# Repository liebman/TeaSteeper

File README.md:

# TeaSteeper

TeaSteeper is a simple device to prevent tea from being over steeped.

- [src](src) contains firmware sources
- [kicad](kicad) contains [KiCad](https://www.kicad.org/) design files
- [enclosure](enclosure) contains [FreeCad](https://www.freecadweb.org/) and STL files for the enclosure.
These are designed for a FDM printer with a .4mm nozzle and .2mm layer height.

## Firmware

This project uses [PlatformIO](https://platformio.org/) to build firmware.

## Schematic

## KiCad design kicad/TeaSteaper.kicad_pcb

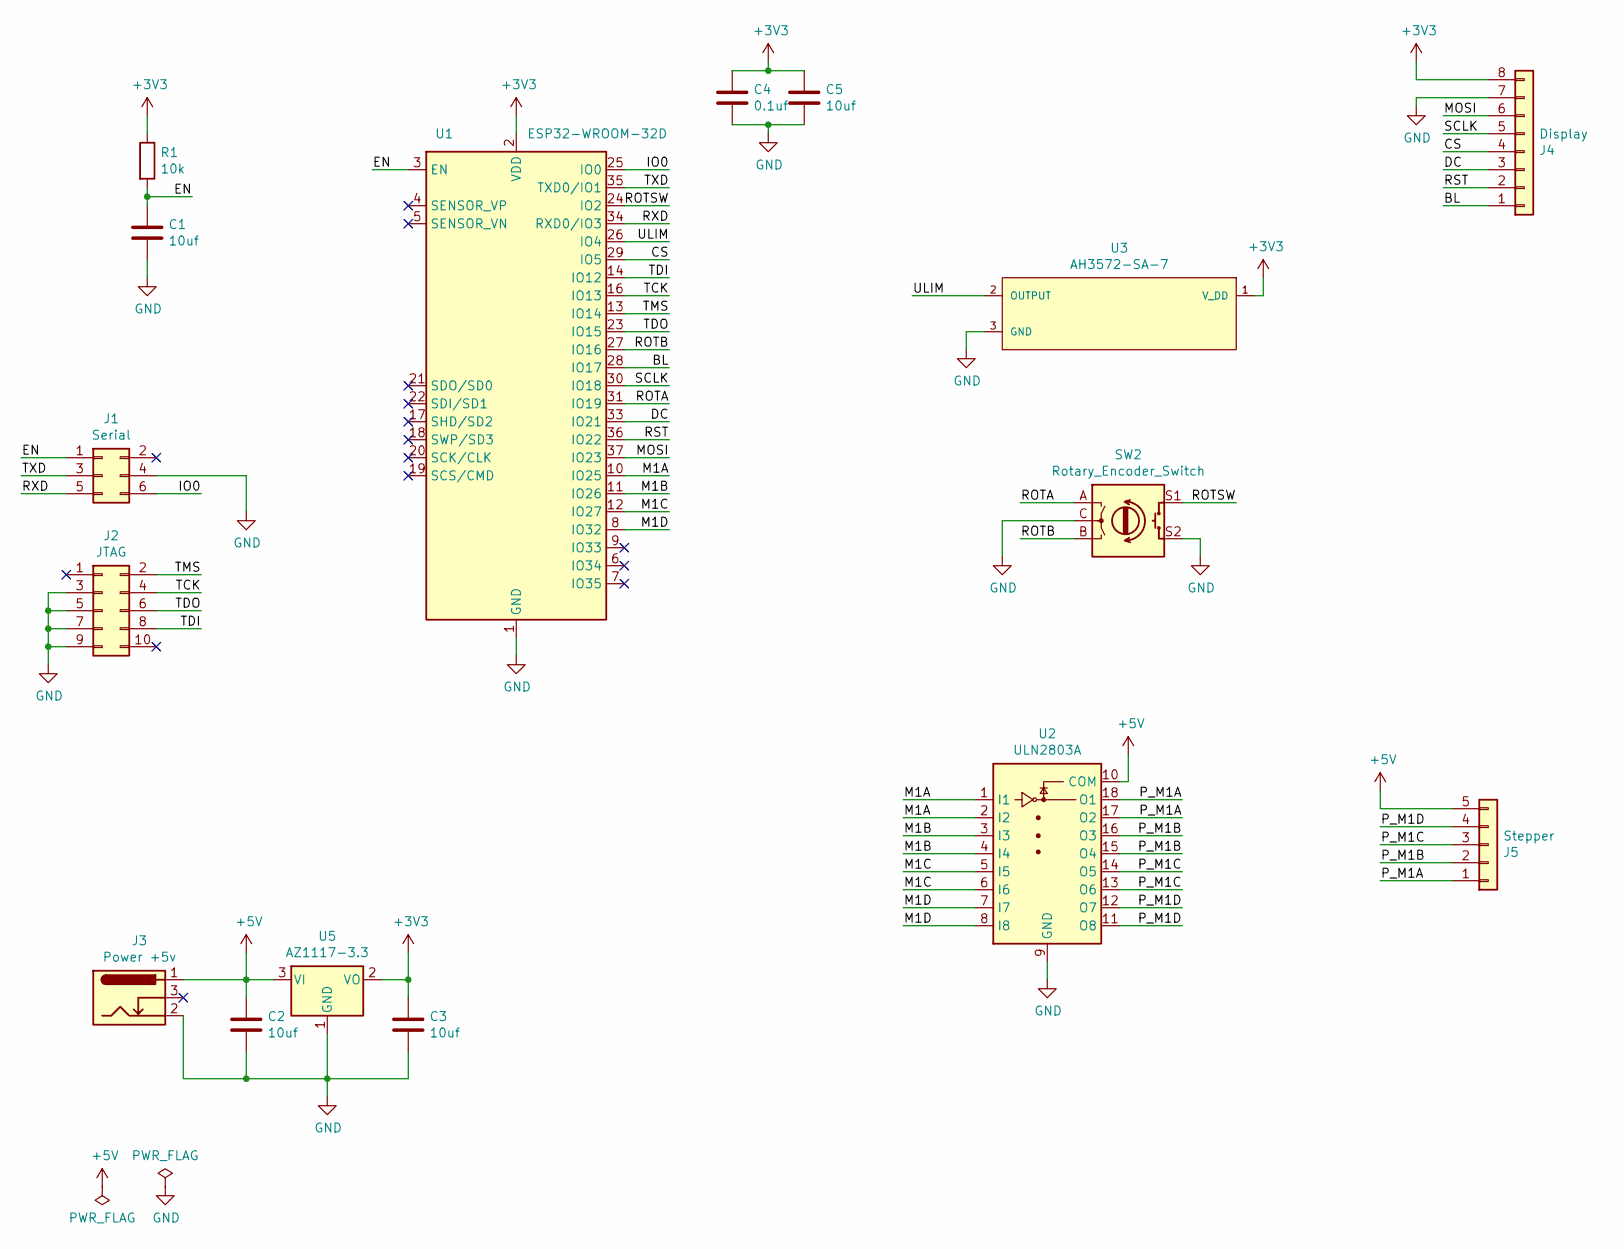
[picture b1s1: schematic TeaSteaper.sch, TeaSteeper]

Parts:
C1, C2, C3, C5: 10uf; C_0805_2012Metric_Pad1.18x1.45mm_HandSolder
C4: 0.1uf; C_0805_2012Metric_Pad1.18x1.45mm_HandSolder
J1: Serial; IDC-Header_2x03_P2.54mm_Vertical
J2: JTAG; IDC-Header_2x05_P2.54mm_Vertical
J3: Power +5v; BarrelJack_CUI_PJ-202A_Horizontal
J4: Display; JST_PH_B8B-PH-K_1x08_P2.00mm_Vertical
J5: Stepper; JST_XH_B5B-XH-A_1x05_P2.50mm_Vertical
R1: 10k; R_0805_2012Metric_Pad1.20x1.40mm_HandSolder
SW2: Rotary_Encoder_Switch; RotaryEncoder_Alps_EC11E-Switch_Vertical_H20mm
U1: ESP32-WROOM-32D; ESP32-WROOM-32
U2: ULN2803A; SOIC-18W_7.5x11.6mm_P1.27mm
U3: AH3572-SA-7; SOT-23; mouser part number 621-AH3572-SA-7; digikey description MAG SWITCH OMNIPOLAR SOT23 T&R
U5: AZ1117-3.3; SOT-223-3_TabPin2

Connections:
+3V3: C3.1, C4.1, C5.1, J4.8, R1.1, U1.2 (VDD), U3.1 (V_DD), U5.2 (VO)
+5V: C2.1, J3.1, J5.5, U2.10 (COM), U5.3 (VI)
/BL: J4.1, U1.28 (IO17)
/CS: J4.4, U1.29 (IO5)
/DC: J4.3, U1.33 (IO21)
/EN: C1.1, J1.1, R1.2, U1.3 (EN)
/IO0: J1.6, U1.25 (IO0)
/M1A: U1.10 (IO25), U2.1 (I1), U2.2 (I2)
/M1B: U1.11 (IO26), U2.3 (I3), U2.4 (I4)
/M1C: U1.12 (IO27), U2.5 (I5), U2.6 (I6)
/M1D: U1.8 (IO32), U2.7 (I7), U2.8 (I8)
/MOSI: J4.6, U1.37 (IO23)
/P_M1A: J5.1, U2.17 (O2), U2.18 (O1)
/P_M1B: J5.2, U2.15 (O4), U2.16 (O3)
/P_M1C: J5.3, U2.13 (O6), U2.14 (O5)
/P_M1D: J5.4, U2.11 (O8), U2.12 (O7)
/ROTA: SW2.A, U1.31 (IO19)
/ROTB: SW2.B, U1.27 (IO16)
/ROTSW: SW2.S1, U1.24 (IO2)
/RST: J4.2, U1.36 (IO22)
/RXD: J1.5, U1.34 (RXD0/IO3)
/SCLK: J4.5, U1.30 (IO18)
/TCK: J2.4, U1.16 (IO13)
/TDI: J2.8, U1.14 (IO12)
/TDO: J2.6, U1.23 (IO15)
/TMS: J2.2, U1.13 (IO14)
/TXD: J1.3, U1.35 (TXD0/IO1)
/ULIM: U1.26 (IO4), U3.2 (OUTPUT)
GND: C1.2, C2.2, C3.2, C4.2, C5.2, J1.4, J2.3, J2.5, J2.7, J2.9, J3.2, J4.7, SW2.C, SW2.S2, U1.1 (GND), U1.15 (GND), U1.38 (GND), U1.39 (GND), U2.9 (GND), U3.3 (GND), U5.1 (GND)

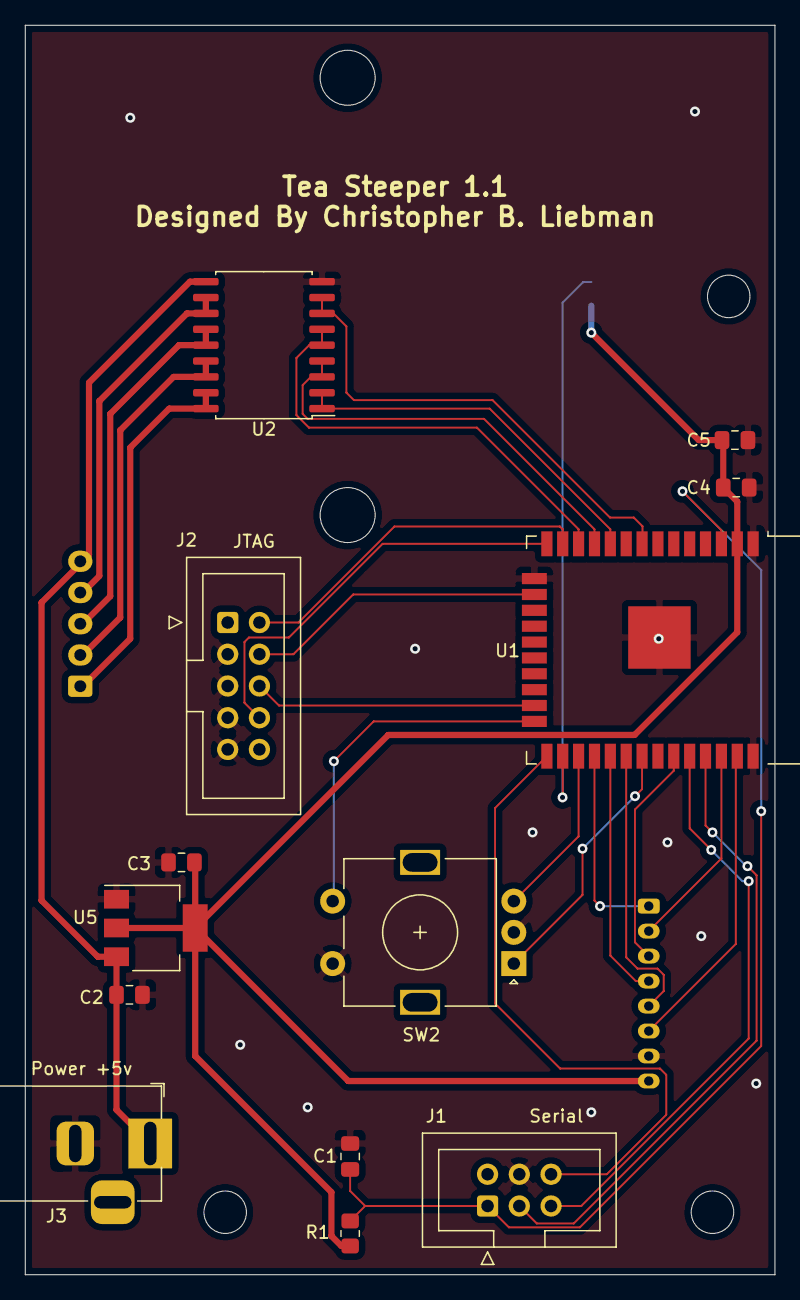
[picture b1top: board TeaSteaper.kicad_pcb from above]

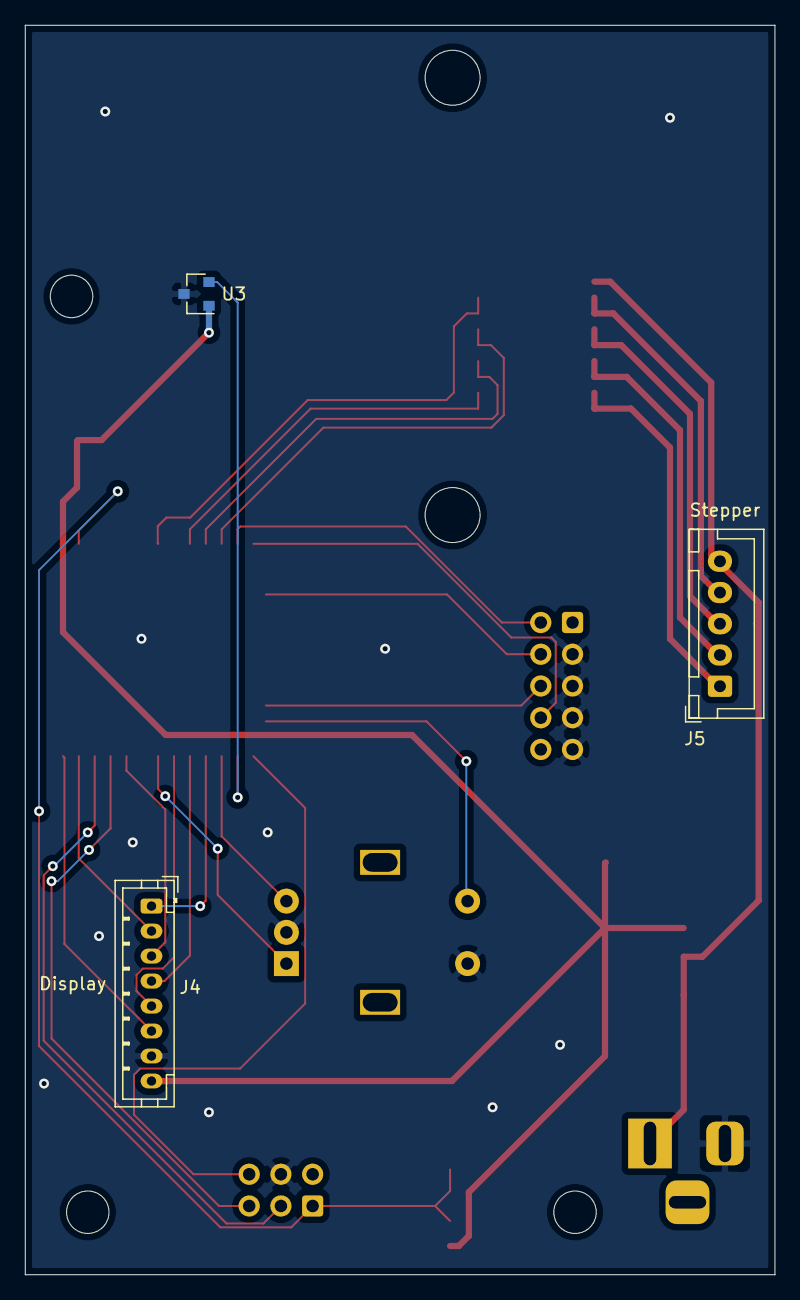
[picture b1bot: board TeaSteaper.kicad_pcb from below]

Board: 2 copper layers, 60.0 x 100.0 mm, 16 parts (3 on the bottom side), 29 nets.

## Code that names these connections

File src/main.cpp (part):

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extern void screensaverLife(TFT_eSPI* tft);

static const char* TAG = "main";
static const uint8_t PIN_ULIM = 4;
static const uint8_t PIN_M1A = 25;
static const uint8_t PIN_M1B = 26;
static const uint8_t PIN_M1C = 27;
static const uint8_t PIN_M1D = 32;
static const uint8_t PIN_ROTSW = 2;
static const uint8_t PIN_ROTA  = 19;
static const uint8_t PIN_ROTB  = 16;

DLog& dlog = DLog::getLog();

static UStepperGPIO io(PIN_M1A, PIN_M1B, PIN_M1C, PIN_M1D, PIN_ULIM);
static UStepper m(io);
static EasyButton button(PIN_ROTSW);
static RotaryEncoder *encoder;
static TFT_eSPI tft;
static ConfigPortal cp;
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
  dlog.info(TAG, "setup: initialze button and encoder");
  button.begin();
  encoder = new RotaryEncoder(PIN_ROTB, PIN_ROTA, RotaryEncoder::LatchMode::FOUR3);
  encoder->setPosition(steep_time);

  dlog.info(TAG, "setup: io begin");
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    dlog.info(TAG, "m.off done!");
  }, 1000);
  delay(2000); // make sure the splash screen is visable for a few seconds
  bool start_config = digitalRead(PIN_ROTSW) == 0;
  if (start_config)
  {
    cp.startPortal("TeaSteeper");
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        dlog.debug(TAG, "loop: start light sleep!");
        delay(100);
        esp_sleep_enable_timer_wakeup(10000000); // sleep 10 seconds at a time
        esp_sleep_enable_ext0_wakeup((gpio_num_t)PIN_ROTSW, 0);
        esp_light_sleep_start();
        dlog.debug(TAG, "loop: wakeup from light sleep!");
      }
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
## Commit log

2021-10-26 1st board layout (changing so want to save this)
2021-10-28 board v1.0 ordered
2021-11-05 firmware functional with no display
2021-11-05 fix typo
2021-11-06 simple display functional
2021-11-06 switch to smaller waveshare 1.14" display
2021-11-06 improve display with a bit of color
2021-11-06 allow cancel during STARTING state
2021-11-06 board v1.1
2021-11-06 added screen saver
2021-11-06 small tweaks
2021-11-07 detect manual shifting of tea arm while idle
2021-11-07 Added firmware update/version/splash screen/long press reset
2021-11-07 added copyright to some files where it was missing
2021-11-07 fix minor issue when canceling screen saver
2021-11-08 added a few dimentions to help enclosure fitting
2021-11-13 added easter egg
2021-11-14 improve easter egg
2021-11-14 added enclosure draft
2021-11-14 adjust stepper mount thickness t fix spacer length
2021-11-17 adjust default time and steps to down position
2021-11-19 small tweaks to enclosure
2021-11-20 Addes simple readme
2021-11-28 add screen blanking when saver ha sbeen on for a while
2021-11-28 improve wakeup a bit, still need a timer.
2021-11-28 improve wakeup added timer
2021-11-30 improve logging
2021-11-30 adjust knob shaft diameter for improved fit.
2021-12-01 cut the log noise from sleep start/end
2021-12-03 test release build
2021-12-03 remove release builds from CI
2021-12-03 move to arduino-esp32 2.0.1
2021-12-03 upgrade TFT_eSPI @ 2.3.84
2021-12-04 vscode always writes extensions.json with crlf

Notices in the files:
src/main.cpp:
MIT License
Copyright (c) 2021 Christopher B. Liebman
